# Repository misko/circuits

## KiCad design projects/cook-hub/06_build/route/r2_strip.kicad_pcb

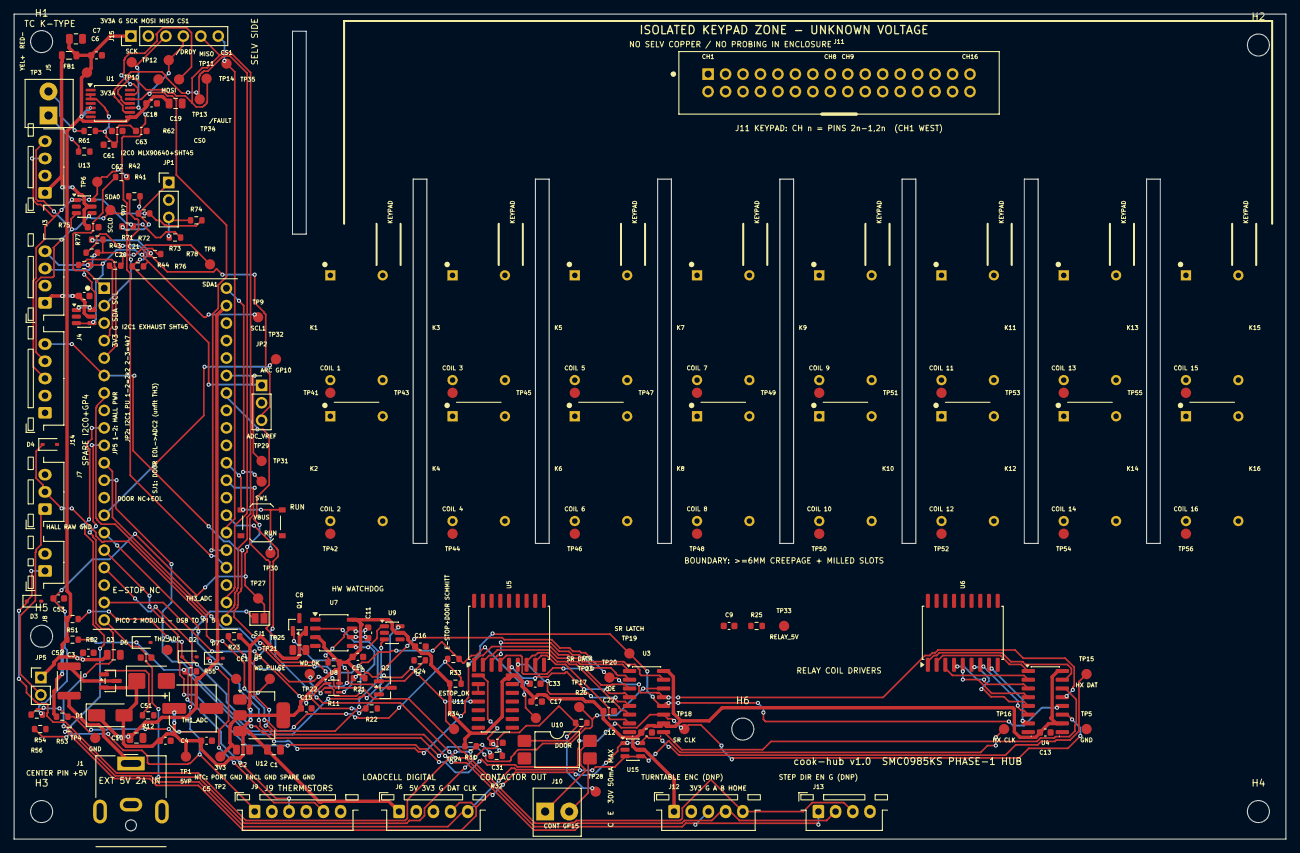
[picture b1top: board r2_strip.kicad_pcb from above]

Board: 4 copper layers, 185.0 x 120.0 mm, 182 parts (0 on the bottom side), 135 nets.

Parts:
C1: 10u LDO in; C_0805_2012Metric
C2, C3: 22u 3V3; C_0805_2012Metric
C4, C5: 22u 5VP; C_0603_1608Metric
C6: 10u 3V3A; C_0805_2012Metric
C7: 100n 3V3A; C_0603_1608Metric
C8: 10u RELAY_5V; C_0805_2012Metric
C9: 100n RELAY_5V; C_0603_1608Metric
C10: 10u VSYS; C_0805_2012Metric
C11: 1u X7R WD; C_0603_1608Metric
C12: 100n U3; C_0603_1608Metric
C13: 100n U4; C_0603_1608Metric
C14: 100n U7; C_0603_1608Metric
C15: 100n U8; C_0603_1608Metric
C16: 100n U9; C_0603_1608Metric
C17: 100n U11; C_0603_1608Metric
C18: 100n U1; C_0603_1608Metric
C19: 10u U1; C_0805_2012Metric
C20: 100n U13; C_0603_1608Metric
C21: 100n U14; C_0603_1608Metric
C22: 100n U15; C_0603_1608Metric
C31: 100n estop RC; C_0603_1608Metric
C33: 100n door RC; C_0603_1608Metric
C51, C52, C53: 100n RC; C_0603_1608Metric
C61: 100n TC diff; C_0603_1608Metric
C62: 10n TC+ cm; C_0603_1608Metric
C63: 10n TC- cm; C_0603_1608Metric
CE1: 220u 16V bulk; CP_Elec_6.3x7.7
D1: SS34 VSYS OR; D_SMA
D2: SMBJ5.0A; D_SMB
D3, D4, D5, D6, D7: PESD5V0S1BA; D_SOD-323
F1: MF-MSMF200L 2A; Fuse_1812_4532Metric
FB1: 600R ferrite; L_0805_2012Metric
H1, H2, H3, H4, H5, H6: MountingHole_3.2mm_M3
J1: EXT 5V 2A; BarrelJack_CUI_PJ-063AH_Horizontal
J2: Pico 2 socket; Pico2_Socket_2x20
J3: I2C0 MLX+SHT45; JST_XH_B4B-XH-A_1x04_P2.50mm_Vertical
J4: I2C1 EXHAUST SHT45; JST_XH_B4B-XH-A_1x04_P2.50mm_Vertical
J5: TC K-TYPE; TerminalBlock_KF350_2P
J6: LOADCELL DIG; JST_XH_B5B-XH-A_1x05_P2.50mm_Vertical
J7: DOOR NC+EOL; JST_XH_B3B-XH-A_1x03_P2.50mm_Vertical
J8: E-STOP NC; JST_XH_B2B-XH-A_1x02_P2.50mm_Vertical
J9: NTC x3; JST_XH_B6B-XH-A_1x06_P2.50mm_Vertical
J10: CONTACTOR 30V; TerminalBlock_KF350_2P
J11: X9555WV 2x16 KEYPAD; IDC_2x16_Keyed
J12: ENCODER DNP; JST_XH_B5B-XH-A_1x05_P2.50mm_Vertical
J13: STEP/DIR/EN DNP; JST_XH_B4B-XH-A_1x04_P2.50mm_Vertical
J14: SPARE I2C0+GP4; JST_XH_B5B-XH-A_1x05_P2.50mm_Vertical
J15: MAX31865 DNP; PinHeader_1x06_P2.54mm_Vertical
JP1: I2C0 PU 2k2|4k7; PinHeader_1x03_P2.54mm_Vertical
JP2: I2C1 PU 2k2|4k7; PinHeader_1x03_P2.54mm_Vertical
JP5: HALL 3V3 opt; PinHeader_1x02_P2.54mm_Vertical
K1, K2, K3, K4, K5, K6, K7, K8, K9, K10, K11, K12, K13, K14, K15, K16: DIP05-1A72-12L; Relay_StandexDIP_1A_pinout12
Q1: AO3401A hi-side; SOT-23
Q2: 2N7002; SOT-23
Q3: AO3401A rev-prot; SOT-23
R11: 390k 1% WD; R_0603_1608Metric
R12: 100k Q3 gate; R_0603_1608Metric
R21: 10k /OE pu; R_0603_1608Metric
R22: 10k RLY_EN pd; R_0603_1608Metric
R23: 47k Q1 pu; R_0603_1608Metric
R24: 1k Q2 gate; R_0603_1608Metric
R25: 10k bleed; R_0603_1608Metric
R26: 330R opto LED; R_0603_1608Metric
R31: 3k3 estop pu; R_0603_1608Metric
R32: 10k estop RC; R_0603_1608Metric
R33: 3k3 door pu; R_0603_1608Metric
R34: 10k door RC; R_0603_1608Metric
R41: 33R SDA0; R_0603_1608Metric
R42: 33R SCL0; R_0603_1608Metric
R43: 33R SDA1; R_0603_1608Metric
R44: 33R SCL1; R_0603_1608Metric
R51, R52, R53: 10k 1% ref; R_0603_1608Metric
R54, R55, R56: 1k RC; R_0603_1608Metric
R61: 100R TC+; R_0603_1608Metric
R62: 100R TC-; R_0603_1608Metric
R71: 2k2 SDA0 pu; R_0603_1608Metric
R72: 2k2 SCL0 pu; R_0603_1608Metric
R73: 4k7 SDA0 pu; R_0603_1608Metric
R74: 4k7 SCL0 pu; R_0603_1608Metric
R75: 2k2 SDA1 pu; R_0603_1608Metric
R76: 2k2 SCL1 pu; R_0603_1608Metric
R77: 4k7 SDA1 pu; R_0603_1608Metric
R78: 4k7 SCL1 pu; R_0603_1608Metric
SJ1: DOOR->ADC2 opt; SolderJumper-2_P1.3mm_Open_Pad1.0x1.5mm
SW1: RUN reset; SW_Push_1P1T_XKB_TS-1187A
TP1: TP 5VP; TestPoint_Pad_D1.5mm
TP2: TP 3V3; TestPoint_Pad_D1.5mm
TP3: TP 3V3A; TestPoint_Pad_D1.5mm
TP4, TP5: TP GND; TestPoint_Pad_D1.5mm
TP6: TP SDA0; TestPoint_Pad_D1.5mm
TP7: TP SCL0; TestPoint_Pad_D1.5mm
TP8: TP SDA1; TestPoint_Pad_D1.5mm
TP9: TP SCL1; TestPoint_Pad_D1.5mm
TP10: TP SCK; TestPoint_Pad_D1.5mm
TP11: TP MISO; TestPoint_Pad_D1.5mm
TP12: TP MOSI; TestPoint_Pad_D1.5mm
TP13: TP CS0; TestPoint_Pad_D1.5mm
TP14: TP CS1; TestPoint_Pad_D1.5mm
TP15: TP HX DAT; TestPoint_Pad_D1.5mm
TP16: TP HX CLK; TestPoint_Pad_D1.5mm
TP17: TP SR DATA; TestPoint_Pad_D1.5mm
TP18: TP SR CLK; TestPoint_Pad_D1.5mm
TP19: TP SR LATCH; TestPoint_Pad_D1.5mm
TP20: TP /OE; TestPoint_Pad_D1.5mm
TP21: TP WD_PULSE; TestPoint_Pad_D1.5mm
TP22: TP WD_OK; TestPoint_Pad_D1.5mm
TP23: TP DOOR; TestPoint_Pad_D1.5mm
TP24: TP ESTOP_OK; TestPoint_Pad_D1.5mm
TP25: TP TH1_ADC; TestPoint_Pad_D1.5mm
TP26: TP TH2_ADC; TestPoint_Pad_D1.5mm
TP27: TP TH3_ADC; TestPoint_Pad_D1.5mm
TP28: TP CONT GP15; TestPoint_Pad_D1.5mm
TP29: TP VBUS; TestPoint_Pad_D1.5mm
TP30: TP RUN; TestPoint_Pad_D1.5mm
TP31: TP ADC_VREF; TestPoint_Pad_D1.5mm
TP32: TP ARC GP10; TestPoint_Pad_D1.5mm
TP33: TP RELAY_5V; TestPoint_Pad_D1.5mm
TP34: TP /DRDY; TestPoint_Pad_D1.5mm
TP35: TP /FAULT; TestPoint_Pad_D1.5mm
TP41: TP COIL 1; TestPoint_Pad_D1.5mm
TP42: TP COIL 2; TestPoint_Pad_D1.5mm
TP43: TP COIL 3; TestPoint_Pad_D1.5mm
TP44: TP COIL 4; TestPoint_Pad_D1.5mm
TP45: TP COIL 5; TestPoint_Pad_D1.5mm
TP46: TP COIL 6; TestPoint_Pad_D1.5mm
TP47: TP COIL 7; TestPoint_Pad_D1.5mm
TP48: TP COIL 8; TestPoint_Pad_D1.5mm
TP49: TP COIL 9; TestPoint_Pad_D1.5mm
TP50: TP COIL 10; TestPoint_Pad_D1.5mm
TP51: TP COIL 11; TestPoint_Pad_D1.5mm
TP52: TP COIL 12; TestPoint_Pad_D1.5mm
TP53: TP COIL 13; TestPoint_Pad_D1.5mm
TP54: TP COIL 14; TestPoint_Pad_D1.5mm
TP55: TP COIL 15; TestPoint_Pad_D1.5mm
TP56: TP COIL 16; TestPoint_Pad_D1.5mm
U1: MAX31856; TSSOP-14_4.4x5mm_P0.65mm
U3: 74HC595 #1; SOIC-16_3.9x9.9mm_P1.27mm
U4: 74HC595 #2; SOIC-16_3.9x9.9mm_P1.27mm
U5: ULN2803A K1-K8; SOIC-18W_7.5x11.6mm_P1.27mm
U6: ULN2803A K9-K16; SOIC-18W_7.5x11.6mm_P1.27mm
U7: SN74LVC1G123; SSOP-8_3.9x5.05mm_P1.27mm
U8: 74LVC1G00 /OE; SOT-353_SC-70-5
U9: 74LVC1G11 AND3; SOT-23-6
U10: LTV-817S; SMDIP-4_W9.53mm
U11: 74HC14 E-stop; SOIC-14_3.9x8.7mm_P1.27mm
U12: AMS1117-3.3; SOT-223-3_TabPin2
U13, U14, U15: USBLC6-2SC6; SOT-23-6

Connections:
3V3: C2.1, C3.1, C12.1, C13.1, C14.1, C15.1, C16.1, C17.1, C20.1, C21.1, C22.1, FB1.1, J3.1, J4.1, J6.2, J12.1, J14.1, JP1.2, JP2.2, JP5.1, R11.2, R21.2, R31.1, R33.1, TP2.1, U3.10, U3.16, U4.10, U4.16, U7.3, U7.8, U8.5, U9.5, U11.14, U12.2, U13.5, U14.5, U15.5
3V3A: C6.1, C7.1, C18.1, C19.1, FB1.2, J15.1, R51.1, R52.1, R53.1, TP3.1, U1.5, U1.8
5VP: C1.1, C4.1, C5.1, CE1.1, D1.2, D2.1, J6.1, Q1.2, Q3.2, R23.2, TP1.1, U12.3
5V_D: F1.2, Q3.3
5V_IN: F1.1, J1.1
ADC_VREF: J2.35, TP31.1
ARC: J2.14, TP32.1
COIL_1: K1.7, TP41.1, U5.18
COIL_2: K2.7, TP42.1, U5.17
COIL_3: K3.7, TP43.1, U5.16
COIL_4: K4.7, TP44.1, U5.15
COIL_5: K5.7, TP45.1, U5.14
COIL_6: K6.7, TP46.1, U5.13
COIL_7: K7.7, TP47.1, U5.12
COIL_8: K8.7, TP48.1, U5.11
COIL_9: K9.7, TP49.1, U6.18
COIL_10: K10.7, TP50.1, U6.17
COIL_11: K11.7, TP51.1, U6.16
COIL_12: K12.7, TP52.1, U6.15
COIL_13: K13.7, TP53.1, U6.14
COIL_14: K14.7, TP54.1, U6.13
COIL_15: K15.7, TP55.1, U6.12
COIL_16: K16.7, TP56.1, U6.11
COIL_EN: R24.1, U9.4
CONT_A: R26.2, U10.1
CONT_C: J10.1, U10.4
CONT_E: J10.2, U10.3
CONT_REQ: J2.20, R26.1, TP28.1
CS0: J2.22, TP13.1, U1.9
CS1: J2.26, J15.6, TP14.1
DOOR_IN: C33.1, J2.11, R34.2, TP23.1
DOOR_RAW: D4.1, J7.2, R33.2, R34.1, SJ1.1
DRDY_N: TP34.1, U1.7
DRV1: U3.15, U5.1
DRV2: U3.1, U5.2
DRV3: U3.2, U5.3
DRV4: U3.3, U5.4
DRV5: U3.4, U5.5
DRV6: U3.5, U5.6
DRV7: U3.6, U5.7
DRV8: U3.7, U5.8
DRV9: U4.15, U6.1
DRV10: U4.1, U6.2
DRV11: U4.2, U6.3
DRV12: U4.3, U6.4
DRV13: U4.4, U6.5
DRV14: U4.5, U6.6
DRV15: U4.6, U6.7
DRV16: U4.7, U6.8
ESTOP_F: C31.1, R32.2, U11.1
ESTOP_INV: U11.2, U11.3
ESTOP_OK: J2.12, TP24.1, U9.3, U11.4
ESTOP_RAW: D3.1, J8.1, R31.2, R32.1
FAULT_N: TP35.1, U1.13
GND: C1.2, C2.2, C3.2, C4.2, C5.2, C6.2, C7.2, C8.2, C9.2, C10.2, C12.2, C13.2, C14.2, C15.2, C16.2, C17.2, C18.2, C19.2, C20.2, C21.2, C22.2, C31.2, C33.2, C51.2, C52.2, C53.2, C62.2, C63.2, CE1.2, D2.2, D3.2, D4.2, D5.2, D6.2, D7.2, J1.2, J2.3, J2.8, J2.13, J2.18, J2.23, J2.28, J2.33, J2.38, J3.2, J4.2, J6.3, J7.3, J8.2, J9.2, J9.4, J9.6, J12.2, J13.4, J14.2, J15.2, Q2.2, R12.2, R22.2, R25.2, SW1.2, TP4.1, TP5.1, U1.1, U1.14, U3.8, U4.8, U5.9, U6.9, U7.1, U7.4, U8.3, U9.2, U10.2, U11.5, U11.7, U11.9, U11.11, U11.13, U12.1, U13.2, U14.2, U15.2
GP4_SPARE: J2.6, J12.5, J13.3, J14.5
HALL_PWR: J7.1, JP5.2
HX_CLK: J2.10, J6.5, TP16.1, U15.3, U15.4
HX_DAT: J2.9, J6.4, TP15.1, U15.1, U15.6
KC1A: J11.1, K1.14
KC1B: J11.2, K1.8
KC2A: J11.3, K2.14
KC2B: J11.4, K2.8
KC3A: J11.5, K3.14
KC3B: J11.6, K3.8
KC4A: J11.7, K4.14
KC4B: J11.8, K4.8
KC5A: J11.9, K5.14
KC5B: J11.10, K5.8
KC6A: J11.11, K6.14
KC6B: J11.12, K6.8
KC7A: J11.13, K7.14
KC7B: J11.14, K7.8
KC8A: J11.15, K8.14
KC8B: J11.16, K8.8
KC9A: J11.17, K9.14
KC9B: J11.18, K9.8
KC10A: J11.19, K10.14
KC10B: J11.20, K10.8
KC11A: J11.21, K11.14
KC11B: J11.22, K11.8
KC12A: J11.23, K12.14
KC12B: J11.24, K12.8
KC13A: J11.25, K13.14
KC13B: J11.26, K13.8
KC14A: J11.27, K14.14
KC14B: J11.28, K14.8
KC15A: J11.29, K15.14
KC15B: J11.30, K15.8
KC16A: J11.31, K16.14
KC16B: J11.32, K16.8
MISO: J2.21, J15.5, TP11.1, U1.11
MOSI: J2.25, J15.4, TP12.1, U1.12
OE_N: R21.1, TP20.1, U3.13, U4.13, U8.4
PU0_22: JP1.1, R71.1, R72.1
PU0_47: JP1.3, R73.1, R74.1
PU1_22: JP2.1, R75.1, R76.1
PU1_47: JP2.3, R77.1, R78.1
Q1G: Q1.1, Q2.3, R23.1
Q2G: Q2.1, R24.2
Q3G: Q3.1, R12.1
RELAY_5V: C8.1, C9.1, K1.1, K2.1, K3.1, K4.1, K5.1, K6.1, K7.1, K8.1, K9.1, K10.1, K11.1, K12.1, K13.1, K14.1, K15.1, K16.1, Q1.3, R25.1, TP33.1, U5.10, U6.10
RLY_EN: J2.19, R22.1, U8.1, U9.6
RUN: J2.30, SW1.1, TP30.1
SCK: J2.24, J15.3, TP10.1, U1.10
SCL0: J2.2, R42.1
SCL0_J: J3.4, J14.4, R42.2, R72.2, R74.2, TP7.1, U13.3, U13.4
SCL1: J2.5, R44.1
SCL1_J: J4.4, R44.2, R76.2, R78.2, TP9.1, U14.3, U14.4
SDA0: J2.1, R41.1
SDA0_J: J3.3, J14.3, R41.2, R71.2, R73.2, TP6.1, U13.1, U13.6
SDA1: J2.4, R43.1
SDA1_J: J4.3, R43.2, R75.2, R77.2, TP8.1, U14.1, U14.6
SR_CASC: U3.9, U4.14
SR_CLK: J2.16, TP18.1, U3.11, U4.11
SR_DATA: J2.15, TP17.1, U3.14
SR_LATCH: J2.17, TP19.1, U3.12, U4.12
TC_MINUS_J: J5.2, R62.1
TC_N: C61.2, C63.1, R62.2, U1.2, U1.3
TC_P: C61.1, C62.1, R61.2, U1.4
TC_PLUS_J: J5.1, R61.1
TH1: D5.1, J9.1, R51.2, R54.1
TH1_ADC: C51.1, J2.31, R54.2, TP25.1
TH2: D6.1, J9.3, R52.2, R55.1
TH2_ADC: C52.1, J2.32, R55.2, TP26.1
TH3: D7.1, J9.5, R53.2, R56.1
TH3_ADC: C53.1, J2.34, R56.2, SJ1.2, TP27.1
TT_A: J2.27, J12.3, J13.1
TT_B: J2.29, J12.4, J13.2
VBUS_PICO: J2.40, TP29.1
VSYS: C10.1, D1.1, J2.39
WD_CX: C11.1, U7.6
WD_OK: TP22.1, U7.5, U8.2, U9.1
WD_PULSE: J2.7, TP21.1, U7.2
WD_RCX: C11.2, R11.1, U7.7

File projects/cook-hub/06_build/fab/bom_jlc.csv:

Comment,Designator,Footprint,MPN,LCSC
100R,"R61,R62",R_0603_1608Metric,,C22775
100k Q3 gate,R12,R_0603_1608Metric,,C25803
100n,"C12,C13,C14,C15,C16,C17,C18,C20,C21,C22,C31,C33,C51,C52,C53,C61,C7,C9",C_0603_1608Metric,,C14663
10k,"R21,R22,R25,R32,R34,R51,R52,R53",R_0603_1608Metric,,C98220
10n,"C62,C63",C_0603_1608Metric,,C57112
10u,"C1,C10,C19,C6,C8",C_0805_2012Metric,,C15850
1k,"R24,R54,R55,R56",R_0603_1608Metric,,C21190
1u X7R WD,C11,C_0603_1608Metric,,C15849
220u 16V bulk,CE1,CP_Elec_6.3x7.7,RVT220UF16V67RV0015,C2887273
22u 3V3,"C2,C3",C_0805_2012Metric,,C45783
22u 5VP,"C4,C5",C_0603_1608Metric,,C59461
2N7002,Q2,SOT-23,2N7002,C8545
2k2,"R71,R72,R75,R76",R_0603_1608Metric,,C4190
330R opto LED,R26,R_0603_1608Metric,,C23138
33R,"R41,R42,R43,R44",R_0603_1608Metric,,C23140
390k 1% WD,R11,R_0603_1608Metric,,C23150
3k3,"R31,R33",R_0603_1608Metric,,C22978
47k Q1 pu,R23,R_0603_1608Metric,,C25819
4k7,"R73,R74,R77,R78",R_0603_1608Metric,,C23162
600R ferrite,FB1,L_0805_2012Metric,GZ2012D601TF,C1017
74HC14 E-stop,U11,SOIC-14_3.9x8.7mm_P1.27mm,SN74HC14DR,C6820
74HC595,"U3,U4",SOIC-16_3.9x9.9mm_P1.27mm,SN74HC595DR,C10092
74LVC1G00 /OE,U8,SOT-353_SC-70-5,SN74LVC1G00DCKR,C8185
74LVC1G11 AND3,U9,SOT-23-6,SN74LVC1G11DBVR,C22046
AMS1117-3.3,U12,SOT-223-3_TabPin2,AMS1117-3.3,C6186
AO3401A,"Q1,Q3",SOT-23,AO3401A,C15127
CONTACTOR 30V,J10,TerminalBlock_KF350_2P,,
DIP05-1A72-12L,"K1,K10,K11,K12,K13,K14,K15,K16,K2,K3,K4,K5,K6,K7,K8,K9",Relay_StandexDIP_1A_pinout12,,
DOOR NC+EOL,J7,JST_XH_B3B-XH-A_1x03_P2.50mm_Vertical,B3B-XH-A(LF)(SN),C144394
DOOR->ADC2 opt,SJ1,SolderJumper-2_P1.3mm_Open_Pad1.0x1.5mm,,
E-STOP NC,J8,JST_XH_B2B-XH-A_1x02_P2.50mm_Vertical,B2B-XH-A(LF)(SN),C158012
EXT 5V 2A,J1,BarrelJack_CUI_PJ-063AH_Horizontal,,
HALL 3V3 opt,JP5,PinHeader_1x02_P2.54mm_Vertical,,
I2C0 MLX+SHT45 / I2C1 EXHAUST SHT45,"J3,J4",JST_XH_B4B-XH-A_1x04_P2.50mm_Vertical,B4B-XH-A(LF)(SN),C144395
I2C0 PU 2k2|4k7,JP1,PinHeader_1x03_P2.54mm_Vertical,,
I2C1 PU 2k2|4k7,JP2,PinHeader_1x03_P2.54mm_Vertical,,
LOADCELL DIG / SPARE I2C0+GP4,"J14,J6",JST_XH_B5B-XH-A_1x05_P2.50mm_Vertical,B5B-XH-A(LF)(SN),C157991
LTV-817S,U10,SMDIP-4_W9.53mm,LTV-817S-TA1,C125121
MAX31856,U1,TSSOP-14_4.4x5mm_P0.65mm,MAX31856MUD+T,C2653162
MF-MSMF200L 2A,F1,Fuse_1812_4532Metric,MF-MSMF200L-2,C89650
NTC x3,J9,JST_XH_B6B-XH-A_1x06_P2.50mm_Vertical,,
PESD5V0S1BA,"D3,D4,D5,D6,D7",D_SOD-323,PESD5V0S1BA,C5158048
Pico 2 socket,J2,Pico2_Socket_2x20,,
RUN reset,SW1,SW_Push_1P1T_XKB_TS-1187A,TS-1187A-B-A-B,C318884
SMBJ5.0A,D2,D_SMB,SMBJ5.0A,C113974
SN74LVC1G123,U7,SSOP-8_2.95x2.8mm_P0.65mm,,C123302
SS34 VSYS OR,D1,D_SMA,SS34,C8678
TC K-TYPE,J5,TerminalBlock_KF350_2P,,
ULN2803A,"U5,U6",SOIC-18W_7.5x11.6mm_P1.27mm,ULN2803ADWR,C9683
USBLC6-2SC6,"U13,U14,U15",SOT-23-6,USBLC6-2SC6,C7519
X9555WV 2x16 KEYPAD,J11,IDC_2x16_Keyed,,

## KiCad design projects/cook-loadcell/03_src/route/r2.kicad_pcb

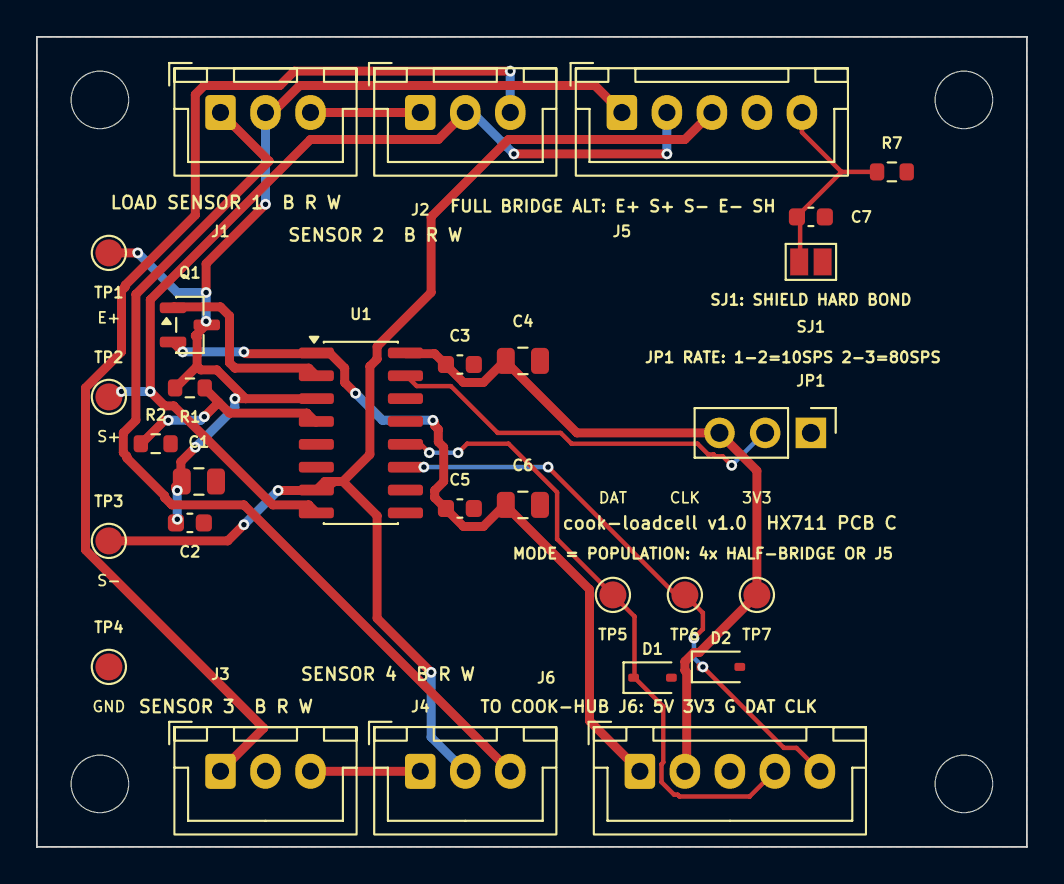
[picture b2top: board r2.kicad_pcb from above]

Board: 2 copper layers, 55.0 x 45.0 mm, 33 parts (0 on the bottom side), 16 nets.

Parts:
C1: 10u E+; C_0805_2012Metric
C2: 100n E+; C_0603_1608Metric
C3: 100n DVDD; C_0603_1608Metric
C4: 10u 3V3; C_0805_2012Metric
C5: 100n VSUP; C_0603_1608Metric
C6: 10u 5V; C_0805_2012Metric
C7: 100n shield bond; C_0603_1608Metric
D1, D2: PESD5V0S1BA; D_SOD-323
H1, H2, H3, H4: MountingHole_3.2mm_M3
J1: SENSOR 1 B/R/W; JST_XH_B3B-XH-A_1x03_P2.50mm_Vertical
J2: SENSOR 2 B/R/W; JST_XH_B3B-XH-A_1x03_P2.50mm_Vertical
J3: SENSOR 3 B/R/W; JST_XH_B3B-XH-A_1x03_P2.50mm_Vertical
J4: SENSOR 4 B/R/W; JST_XH_B3B-XH-A_1x03_P2.50mm_Vertical
J5: FULL BRIDGE ALT; JST_XH_B5B-XH-A_1x05_P2.50mm_Vertical
J6: TO HUB J6; JST_XH_B5B-XH-A_1x05_P2.50mm_Vertical
JP1: RATE 1-2=10SPS 2-3=80; PinHeader_1x03_P2.54mm_Vertical
Q1: S8550; SOT-23
R1: 20k 1% AVDD-VFB; R_0603_1608Metric
R2: 8.2k 1% VFB-GND; R_0603_1608Metric
R7: 100R shield bond; R_0603_1608Metric
SJ1: SH hard bond DNP; SolderJumper-2_P1.3mm_Open_Pad1.0x1.5mm
TP1: TP E+; TestPoint_Pad_D1.5mm
TP2: TP S+; TestPoint_Pad_D1.5mm
TP3: TP S-; TestPoint_Pad_D1.5mm
TP4: TP GND; TestPoint_Pad_D1.5mm
TP5: TP DAT; TestPoint_Pad_D1.5mm
TP6: TP CLK; TestPoint_Pad_D1.5mm
TP7: TP 3V3; TestPoint_Pad_D1.5mm
U1: HX711; SOIC-16_3.9x9.9mm_P1.27mm

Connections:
3V3: C3.1, C4.1, J6.2, JP1.3, TP7.1, U1.16
5V: C5.1, C6.1, J6.1, Q1.2, U1.1
AVDD_FB: R1.2, R2.1, U1.4
BASE: Q1.1, U1.2
CLK: D2.1, J6.5, TP6.1, U1.11
DAT: D1.1, J6.4, TP5.1, U1.12
E_PLUS: C1.1, C2.1, J1.2, J5.1, Q1.3, R1.1, TP1.1, U1.3
GND: C1.2, C2.2, C3.2, C4.2, C5.2, C6.2, C7.2, D1.2, D2.2, J3.2, J5.4, J6.3, JP1.1, R2.2, R7.2, SJ1.2, TP4.1, U1.5, U1.9, U1.10, U1.14
RATE_SEL: JP1.2, U1.15
RING_12: J1.3, J2.1
RING_23: J2.3, J3.1
RING_34: J3.3, J4.1
RING_41: J1.1, J4.3
SH: C7.1, J5.5, R7.1, SJ1.1
S_MINUS: J4.2, J5.3, TP3.1, U1.7
S_PLUS: J2.2, J5.2, TP2.1, U1.8
